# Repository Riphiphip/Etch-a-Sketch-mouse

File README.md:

# Etch-a-Sketch-mouse

Custom computer mouse to be controlled like an Etch-a-sketch.

Heavily inspired by Mitxela https://mitxela.com/projects/etch_mouse

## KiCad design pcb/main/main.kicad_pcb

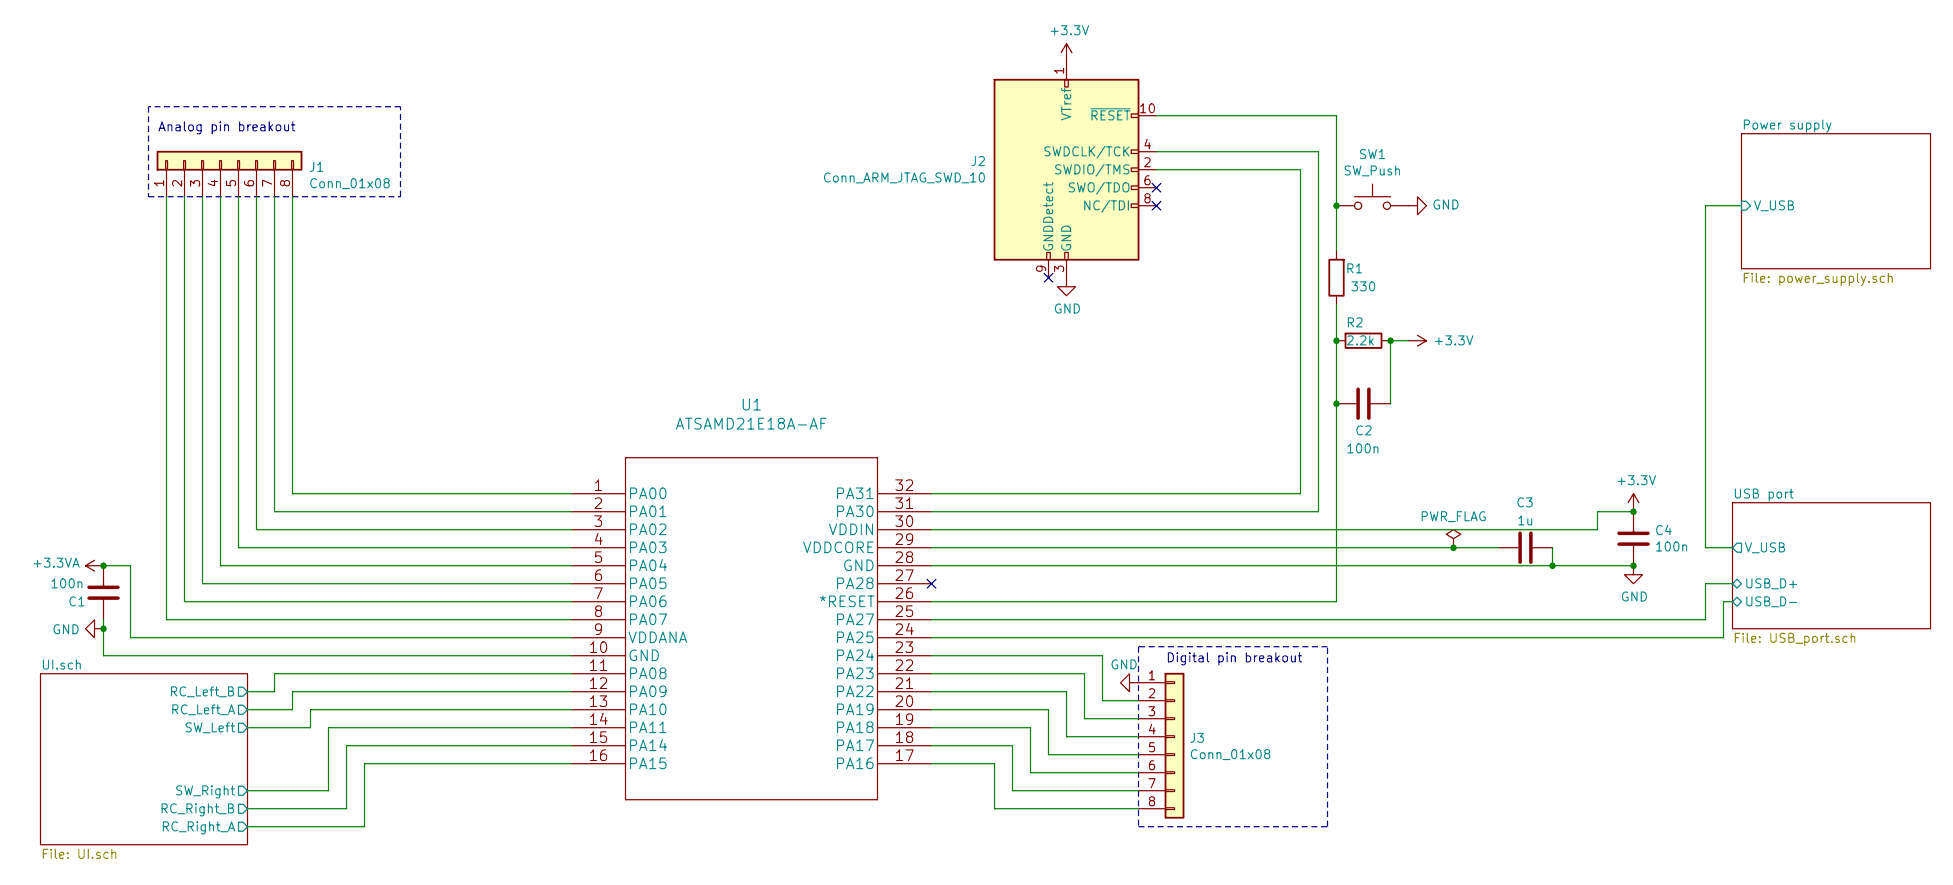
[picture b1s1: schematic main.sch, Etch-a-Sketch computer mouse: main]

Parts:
C1, C2, C4: 100n; C_0603_1608Metric_Pad1.08x0.95mm_HandSolder
C3: 1u; C_0805_2012Metric_Pad1.18x1.45mm_HandSolder
J1, J3: Conn_01x08; PinHeader_1x08_P2.54mm_Vertical
J2: Conn_ARM_JTAG_SWD_10; PinHeader_2x05_P1.27mm_Vertical_SMD
R1: 330; R_0603_1608Metric_Pad0.98x0.95mm_HandSolder
R2: 2.2k; R_0603_1608Metric_Pad0.98x0.95mm_HandSolder
SW1: SW_Push; SW_Push_1P1T_NO_6x6mm_H9.5mm
U1: ATSAMD21E18A-AF

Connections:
+3.3VA: C1.1, U1.9 (VDDANA); also elsewhere on the board
/UI.sch/RC_Left_A: U1.12 (PA09); also elsewhere on the board
/UI.sch/RC_Left_B: U1.11 (PA08); also elsewhere on the board
/UI.sch/RC_Right_A: U1.16 (PA15); also elsewhere on the board
/UI.sch/RC_Right_B: U1.15 (PA14); also elsewhere on the board
/UI.sch/SW_Left: U1.13 (PA10); also elsewhere on the board
/UI.sch/SW_Right: U1.14 (PA11); also elsewhere on the board
/USB port/USB_D+: U1.25 (PA27); also elsewhere on the board
/USB port/USB_D-: U1.24 (PA25); also elsewhere on the board
GND: C1.2, C3.2, C4.2, J2.3 (GND), J2.5 (GND), J3.1, SW1.2, U1.10 (GND), U1.28 (GND); also elsewhere on the board
unnamed: C2.2, R1.1, R2.2, U1.26 (*RESET)
unnamed: C3.1, U1.29 (VDDCORE)
unnamed: J1.1, U1.8 (PA07)
unnamed: J1.2, U1.7 (PA06)
unnamed: J1.3, U1.6 (PA05)
unnamed: J1.4, U1.5 (PA04)
unnamed: J1.5, U1.4 (PA03)
unnamed: J1.6, U1.3 (PA02)
unnamed: J1.7, U1.2 (PA01)
unnamed: J1.8, U1.1 (PA00)
unnamed: J2.2 (SWDIO/TMS), U1.32 (PA31)
unnamed: J2.4 (SWDCLK/TCK), U1.31 (PA30)
unnamed: J2.10 (~RESET~), R1.2, SW1.1
unnamed: J3.2, U1.23 (PA24)
unnamed: J3.3, U1.22 (PA23)
unnamed: J3.4, U1.21 (PA22)
unnamed: J3.5, U1.20 (PA19)
unnamed: J3.6, U1.19 (PA18)
unnamed: J3.7, U1.18 (PA17)
unnamed: J3.8, U1.17 (PA16)

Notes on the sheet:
Analog pin breakout
Digital pin breakout

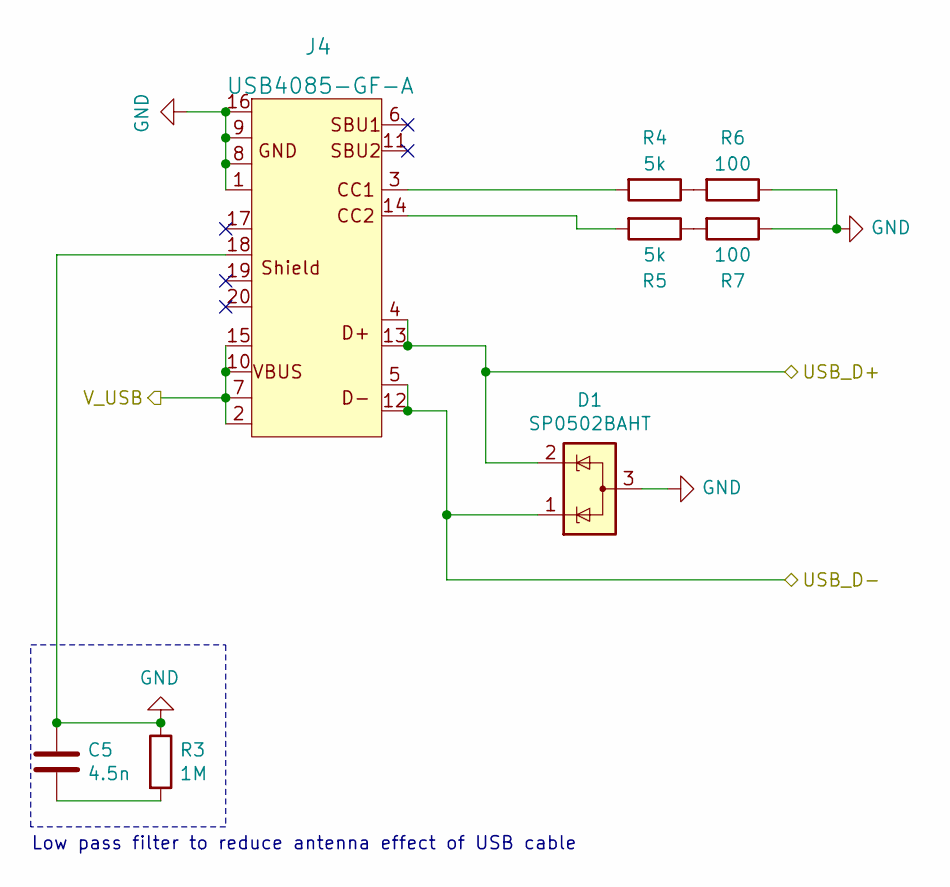
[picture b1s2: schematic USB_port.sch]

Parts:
C5: 4.5n; C_0603_1608Metric_Pad1.08x0.95mm_HandSolder
D1: SP0502BAHT; SOT-23
J4: USB4085-GF-A
R3: 1M; R_0603_1608Metric_Pad0.98x0.95mm_HandSolder
R4, R5: 5k; R_0603_1608Metric_Pad0.98x0.95mm_HandSolder
R6, R7: 100; R_0603_1608Metric_Pad0.98x0.95mm_HandSolder

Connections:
/Power supply/V_USB: J4.2 (VBUS), J4.7 (VBUS), J4.10 (VBUS), J4.15 (VBUS); also elsewhere on the board
/USB port/USB_D+: D1.2 (K), J4.4 (D+), J4.13 (D+); also elsewhere on the board
/USB port/USB_D-: D1.1 (K), J4.5 (D-), J4.12 (D-); also elsewhere on the board
GND: C5.2, D1.3 (A), J4.1 (GND), J4.8 (GND), J4.9 (GND), J4.16 (GND), J4.18 (SHIELD2), R3.1, R6.1, R7.1; also elsewhere on the board
unnamed: C5.1, R3.2
unnamed: J4.3 (CC1), R4.2
unnamed: J4.14 (CC2), R5.2
unnamed: R4.1, R6.2
unnamed: R5.1, R7.2

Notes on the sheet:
Low pass filter to reduce antenna effect of USB cable

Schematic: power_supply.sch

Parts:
C6, C8: 1u; C_0805_2012Metric_Pad1.18x1.45mm_HandSolder
C7: 10u; C_0805_2012Metric_Pad1.18x1.45mm_HandSolder
D2: SMAJ5.0A; D_SMA_Handsoldering
FB1: Ferrite_Bead; R_0603_1608Metric_Pad0.98x0.95mm_HandSolder
J5, J6, J7: Conn_02x02_Odd_Even; PinHeader_2x02_P2.54mm_Vertical
JP1, JP2: Jumper; PinHeader_1x02_P2.54mm_Vertical
U2: LP3990MF-3.3_NOPB; LP3990MF-3.3&slash_NOPB

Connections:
+3.3VA: C7.1, FB1.1; also elsewhere on the board
+5V: J5.1, J5.2, J5.3, J5.4, JP1.1
/Power supply/V_USB: C6.2, D2.1 (A1), JP1.2, U2.1, U2.3; also elsewhere on the board
GND: C6.1, C7.2, C8.2, D2.2 (A2), J7.1, J7.2, J7.3, J7.4, U2.2; also elsewhere on the board
unnamed: C8.1, JP2.2, U2.5

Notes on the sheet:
Noise filtering for analog supply. Probably unnecessary.
Voltage breakouts

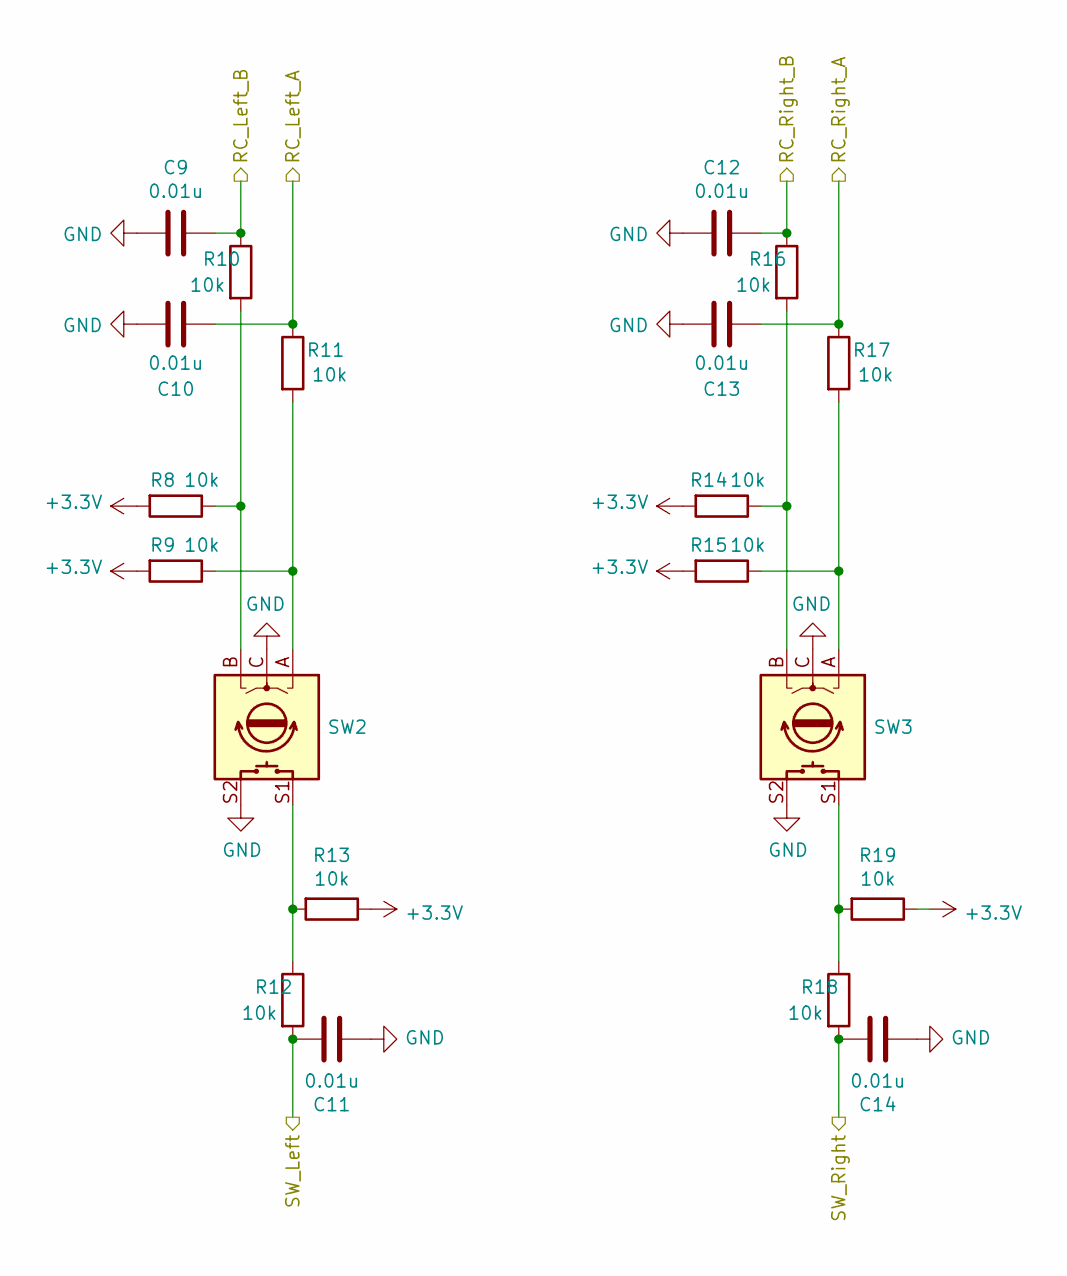
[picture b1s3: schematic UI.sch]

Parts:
C9, C10, C11, C12, C13, C14: 0.01u; C_0603_1608Metric_Pad1.08x0.95mm_HandSolder
R8, R9, R10, R11, R12, R13, R14, R15, R16, R17, R18, R19: 10k; R_0603_1608Metric_Pad0.98x0.95mm_HandSolder
SW2, SW3: Rotary_Encoder_Switch; RotaryEncoder_Alps_EC12E-Switch_Vertical_H20mm

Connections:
/UI.sch/RC_Left_A: C10.1, R11.1; also elsewhere on the board
/UI.sch/RC_Left_B: C9.1, R10.1; also elsewhere on the board
/UI.sch/RC_Right_A: C13.1, R17.1; also elsewhere on the board
/UI.sch/RC_Right_B: C12.1, R16.1; also elsewhere on the board
/UI.sch/SW_Left: C11.1, R12.2; also elsewhere on the board
/UI.sch/SW_Right: C14.1, R18.2; also elsewhere on the board
GND: C9.2, C10.2, C11.2, C12.2, C13.2, C14.2, SW2.C, SW2.S2, SW3.C, SW3.S2; also elsewhere on the board
unnamed: R8.1, R10.2, SW2.B
unnamed: R9.1, R11.2, SW2.A
unnamed: R12.1, R13.2, SW2.S1
unnamed: R14.1, R16.2, SW3.B
unnamed: R15.1, R17.2, SW3.A
unnamed: R18.1, R19.2, SW3.S1

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
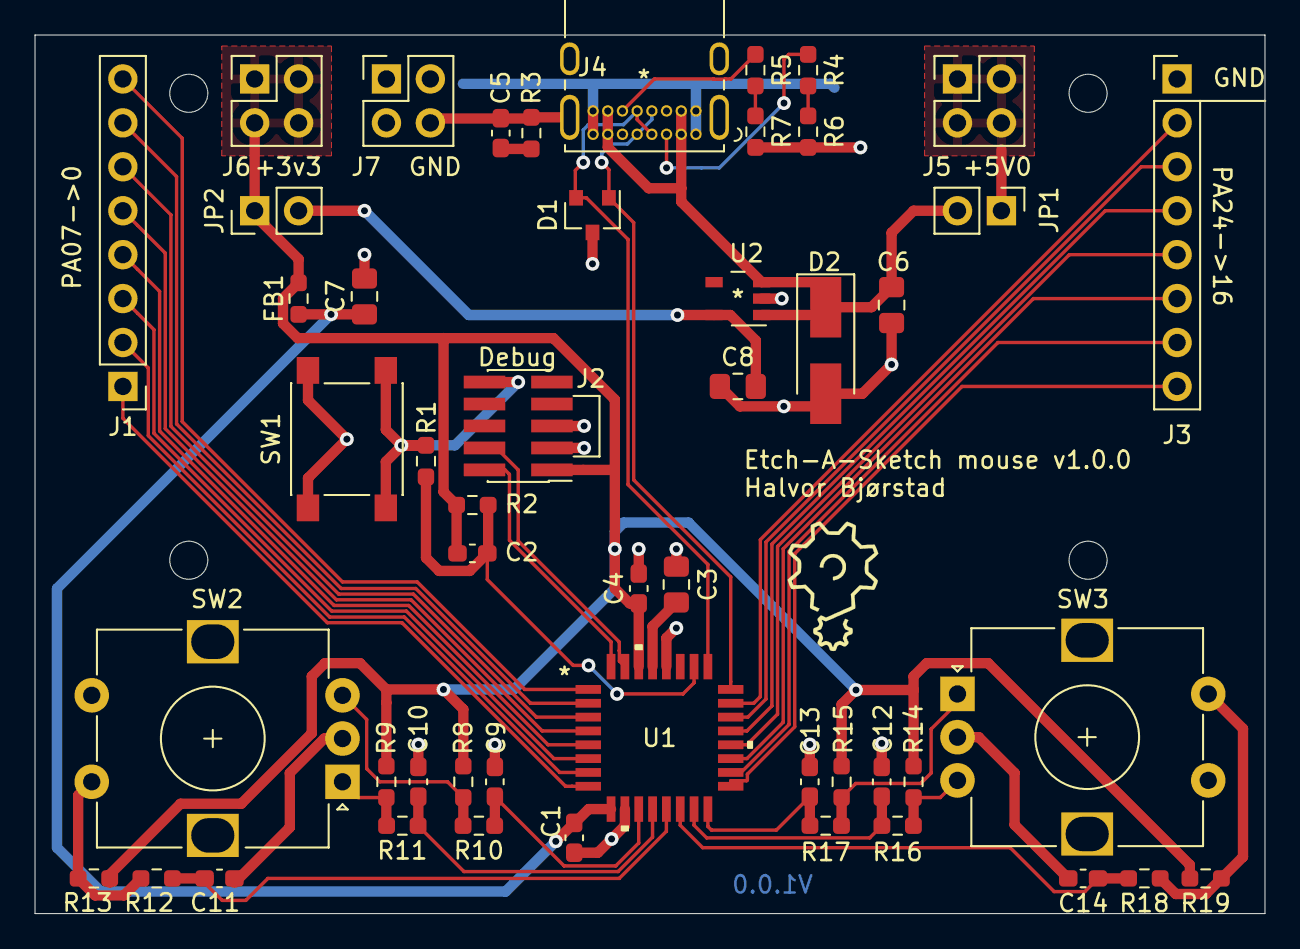
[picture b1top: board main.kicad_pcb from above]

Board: 2 copper layers, 71.1 x 50.8 mm, 50 parts (0 on the bottom side), 45 nets.

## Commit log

2021-11-09 Add blank pcb project
2021-11-09 Source some components
2021-11-12 Added ESD protection to USB
2021-11-22 Complete circuit + footprint association
2021-11-27 Finished PCB layout

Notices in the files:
parts and their libraries:
Copyright 2021 Accelerated Designs. All rights reserved.
